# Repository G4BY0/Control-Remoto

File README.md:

# Remote Controller

### A literal super universal remote controller, you can manipulate TVS, AIR CONDITIONERS, DECODERS and MORE.

The purpose of this project is to have in one room, one infrared remote for everything.

https://github.com/G4BY0/Control-Remoto/blob/af7007d788a45e271489a508236b302a6bf80a4f/Picture.jpeg

## Contents

  -[How it works?](#how-it-works?)
  -[Development Status](#development-status)
  -[Hardware](#hardware)
  -[Dependencies](#dependencies)

## How it works? (Software)

The structure of the stored Infrared signals is:

Example:

* Profile: LG TV
* Subprofile: Turn on

This kind of profiles are stored on the SD, they are separated in diferent files.

Example: LG_TV.db

This files have the binary of infrared signals with the name of their subprofiles.

## Development Status

Latest Stable Release    

Latest Development Release    

## Hardware

* [PCB](https://github.com/G4BY0/Control-Remoto/tree/main/hardware)
* Display Adafruit SH110X
* Six Botons
* [Nodemcu Esp32-S (4MB Flash Memory)](https://docs.ai-thinker.com/_media/esp32/docs/nodemcu-32s_product_specification.pdf)
* Module SD (3.3V, We modded it to work with that voltage)
* BC548 (Battery Medition)
* VS1838 (Infrared Receiver)
* Infrared LED (Infrared Emitter)
* LIPO Battery 3.7-4.2V
* Step Up 1.8v-4.2v to 5V (180mA)
* LIPO Charger USB-C Port
* 2N3904
* Resistors 10K, 10K, 630K (Battery Medition)
* [Six Keycaps](https://github.com/G4BY0/Control-Remoto/tree/main/hardware/STL's)
* [Case](https://github.com/G4BY0/Control-Remoto/tree/main/hardware/STL's)
* Cable USB-C for charging

## Dependencies

* [Adafruit BusIO](https://github.com/adafruit/Adafruit_BusIO)
* [Adafruit GFX Library](https://github.com/adafruit/Adafruit-GFX-Library)
* [Adafruit SH110X](https://github.com/adafruit/Adafruit_SH110x)
* [QRCode](https://www.adafruit.com/products/2471)
* [arduino-esp32](https://www.adafruit.com/products/2471)

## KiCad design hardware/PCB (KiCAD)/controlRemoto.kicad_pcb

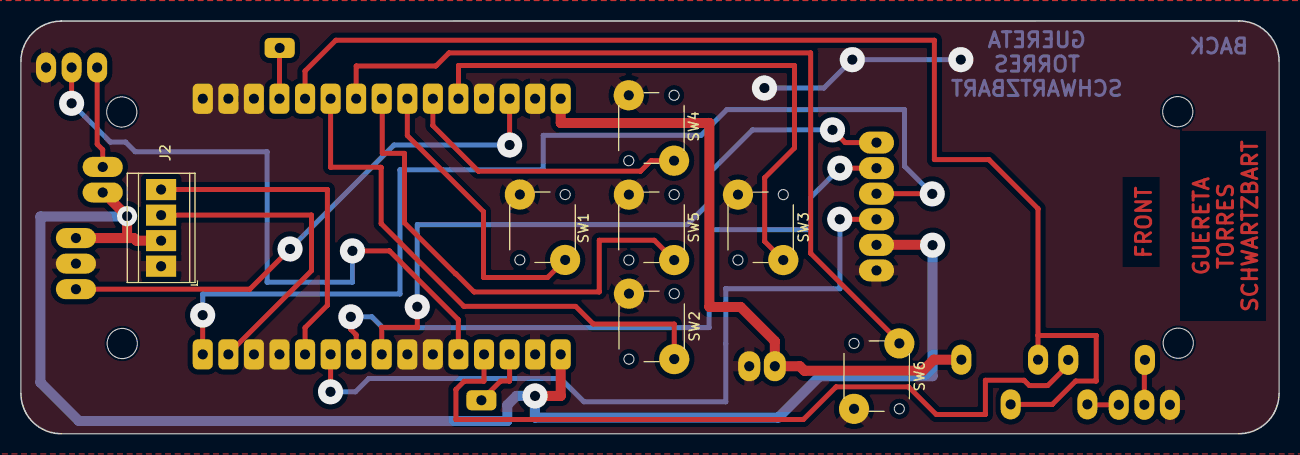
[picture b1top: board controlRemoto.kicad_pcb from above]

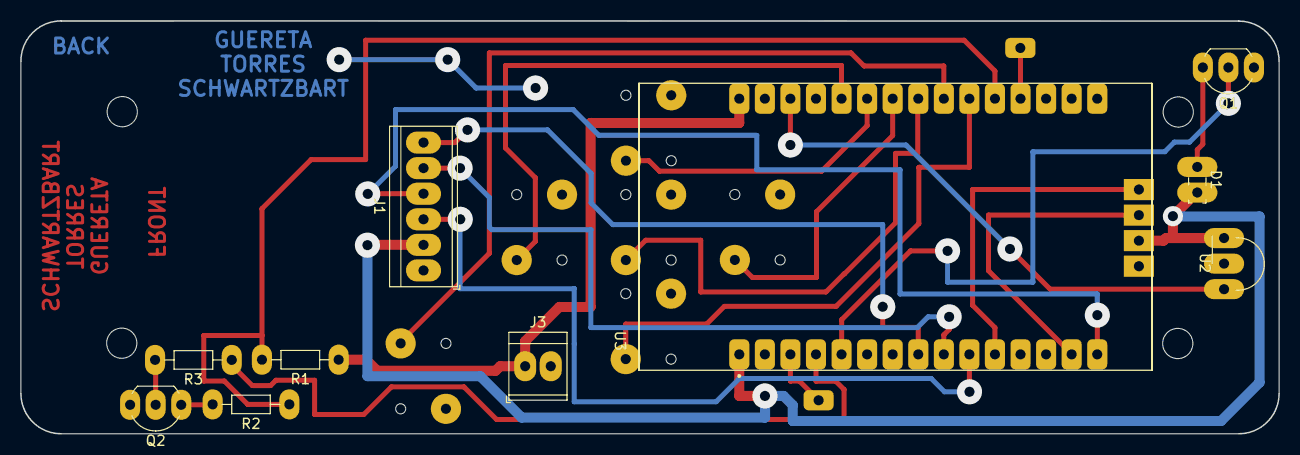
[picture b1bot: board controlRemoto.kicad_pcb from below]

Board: 2 copper layers, 125.0 x 41.0 mm, 17 parts (10 on the bottom side), 22 nets.

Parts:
D1: IR EMISOR; LED_SideEmitter_Rectangular_W4.5mm_H1.6mm
J1: Modulo SD; TerminalBlock_TE_282834-6_1x06_P2.54mm_Horizontal
J2: Display Oled; TerminalBlock_TE_282834-4_1x04_P2.54mm_Horizontal
J3: Bornera; TerminalBlock_TE_282834-2_1x02_P2.54mm_Horizontal
Q1: 2N3904; TO-92_Inline_Wide
Q2: BC546; TO-92_Inline_Wide
R1, R2: 10000; R_Axial_DIN0204_L3.6mm_D1.6mm_P7.62mm_Horizontal
R3: 630000; R_Axial_DIN0204_L3.6mm_D1.6mm_P7.62mm_Horizontal
SW1: ARRIBA; SW_PUSH_6mm_H4.3mm
SW2: IZQUIERDA; SW_PUSH_6mm_H4.3mm
SW3: ABAJO; SW_PUSH_6mm_H4.3mm
SW4: DERECHA; SW_PUSH_6mm_H4.3mm
SW5: ENTER; SW_PUSH_6mm_H4.3mm
SW6: ATRAS; SW_PUSH_6mm_H4.3mm
U2: IR RECEIVER; Vishay_MINIMOLD-3Pin
U3: ESP32-DEVKIT-V1; MODULE_ESP32_DEVKIT_V1

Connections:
3V3: D1.2 (A), J1.2, J2.2, U2.3 (Vs), U3.1 (3V3)
+3V8: J3.1, R1.1, U3.30 (VIN)
D2: R3.1, U3.4 (D2)
D4: Q1.2 (B), U3.5 (D4)
D5: J1.6, U3.8 (D5)
D13: U2.1 (OUT), U3.28 (D13)
D14: SW3.1, U3.26 (D14)
D18: J1.5, U3.9 (D18)
D19: J1.3, U3.10 (D19)
D21: J2.4, U3.11 (D21)
D22: J2.3, U3.14 (D22)
D23: J1.4, U3.15 (D23)
D25: SW5.1, U3.23 (D25)
D26: SW1.1, U3.24 (D26)
D27: SW4.1, U3.25 (D27)
D32: SW2.1, U3.21 (D32)
D33: SW6.1, U3.22 (D33)
D35: R1.2, R2.1, U3.20 (D35)
GND: J1.1, J2.1, J3.2, Q1.1 (E), Q2.3 (E), SW1.2, SW2.2, SW3.2, SW4.2, SW5.2, SW6.2, U2.2 (GND), U3.2 (GND), U3.29 (GND)
unnamed: D1.1 (K), Q1.3 (C)
unnamed: Q2.2 (B), R3.2
unnamed: Q2.1 (C), R2.2

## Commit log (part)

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2023-03-07 Inicio de Proyecto
    Estableciendo parámetros iniciales, ordenando y usando herramientas planteadas en la materia Proyecto Final
2023-03-07 Desarrollado en clase
    Plasme lo desarrollado en clase para luego continuarlo en el instituto
2023-03-07 Desarrollando clase
    Incluyendo librerias y ordenando un toque.
2023-03-07 desarrollo en clase + tutorial
    Introduccion de clases de gaby a melvin y joaco, melvin propuso buenas ideas de la interfaz del tft "los menus"
2023-03-10 Ordenando
2023-03-16 Cambiazo de Display
    Cambiamos de Display TFT 2.2" a OLED 1.3"
2023-03-26 Change of library for driver of display
    display 1.3" OLED
2023-03-26 Desarrollando
2023-03-28 Desarrollando Cursor
2023-03-31 Developing
2023-04-01 Developing
    desarrollo del cursor
2023-04-04 Developing
    Desarrollo en clase 04/04/23
2023-04-06 Developing
    Desarrollo
2023-04-06 Developing
    Desarrollando con los pibes
2023-04-09 Developing
    Desarrollando
2023-04-09 Optimizando
2023-04-10 Developing
    Desarrollando y separando de manera intuitiva el codigo para facil comprension
2023-04-10 Updateado lo que joaco me corrigio
2023-04-10 Ordenando y desarollando
    Infrarrojo, planeando como va a laburar
2023-04-13 Developing
    soy guereta pero desde la cuenta de melvin :))
2023-04-17 Developing
    Desarrollando en grupo
2023-04-20 Developing
    Subo cambios por si hay algun boludo que tiene ganas de molestar, dejaron el celu en porteria porque me lo olvide en el auto y me voy un toq, ahora sigo desarrollando en un rato.
2023-04-21 Ordenando y Arreglando
    arreglando errores y ordenando parte del codigo
2023-04-21 Developin
    desarrollanod
2023-04-24 Ordenando
    Ordenando
2023-04-25 Developping & Fixxing
    Desarrollando y corrigiendo errores
2023-04-27 License
    MIT LICENSE
2023-05-04 Developing
    Desarrollando el manejo de perfiles
2023-05-05 Discutiendo
    Discutiendo como va a ser el desarrollo de los subperfiles y que en la version beta del proyecto, el nombre de los subperfiles va a estar limitado hasta 12 caracteres.
2023-05-11 Developing
    Desarrollando crear y eliminar subperfiles, falta desarrollar un poco mas y tambien el apartado del almacenamiento de los subperfiles para agregar y eliminar
2023-05-14 Cursor WritterV2 + Developing
    Desarrollo de otra clase de Writter y desarrollo en el codigo
2023-05-14 Cursor
    Me olvide de incluir los cambios de Cursor.h
2023-05-16 Developing
    Desarrollando en equipo
2023-05-16 Cambio de pines en el infrarrojo
    Un cambio pequeño pero a la vez crucial
2023-05-16 Pre-Alpha (Modos)
    Configuracion de modos hecha para la version Pre-Alpha
2023-05-21 Developing & Searching for Errors
    Sigo buscando el error de indefiniciones cuando se compila, agregue un par de features mas
2023-05-21 Desarrollando y fixeando bugs
    Problema al terminar el compilado:
    Advanced Memory Usage is available via "PlatformIO Home > Project Inspect"
    Error: The program size (44552 bytes) is greater than maximum allowed (32256 bytes)
    RAM: [====*** [checkprogsize] Explicit exit, status 1
    ======] 151.8% (used 3109 bytes from 2048 bytes)
    Flash: [==========] 138.1% (used 44552 bytes from 32256 bytes)
2023-05-22 Optimizing
    - Se genero una banda de optimización gracias a que las cadenas de caracteres se pueden almacenar en la memoria flash en vez de la ram (utilizando por ejemplo: F() que devuelve: const __FlashStringHe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
    "F() se utiliza para almacenar cadenas de texto en la memoria de programa (flash) en lugar de la memoria RAM. El tipo devuelto por F() es const __FlashStringHelper*, que es un tipo especial definido 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
    La principal diferencia radica en la ubicación de almacenamiento de la cadena de texto. Mientras que const char* almacena la cadena en la memoria RAM, F() almacena la cadena en la m
2023-05-22 Revert "Revert "Merge branch 'main' of https://github.com/G4BY0/Control-Remoto""
    This reverts commit 4b9f240cd9d582058136f83fae59486e599da04a.
2023-05-22 Optimizando
    Optimizando las mierdas que Guereta deja. Miranda nos sirvió de gran ayuda
2023-05-26 Seteando Configs
    - La librería SD como es incompatible con otras arquitecturas que no son AVR, la desinstale y en caso de usar la placa que tenga AVR se usará esa, sino la otra.
2023-05-31 Developing & Correcting Issues
    Arreglado el problema de reinicio en el setup, pero luego hay otro problema que un nucleo hace dump y resetea el sketch... Solucionar pronto
    Guru Meditation Error: Core 1 panic'ed (LoadProhibited). Exception was unhandled.
    Core 1 register dump:
    PC : 0x40087818 PS : 0x00060e30 A0 : 0x800d8014 A1 : 0x3ffb2190
    A2 : 0x00000002 A3 : 0x00000000 A4 : 0x000000ff A5 : 0x0000ff00
    A6 : 0x00ff0000 A7 : 0xff000000 A8 : 0x80104904 A9 : 0x3ffb2150
2023-06-01 IRremote Issues
    Debido a que vamos a usar la placa ESP32S de la marca nodemcu, IRremote no dispone de compatibilidad al esp32... entonces se debera usar otra lamentablemente.
    Esto da lugar a que hay que desarrollar en el apartado de Profiles y Infrared.
2023-06-05 Correcting Issues
    Corrigiendo errores del Writter y WritterV2
2023-06-05 Dev
    Developing & Correcting Issues
2023-06-06 Correcting Issues
    corrigiendo errores en el colegio, sin melvin lamentablemente. porque falto y no aviso >>:(((((
2023-06-13 Desarrollando
    Corrigiendo errores del writter y cursor
2023-06-14 Ordenando y Corrigiendo Errores
    Corrigiendo errores, ordenando y viendo que onda lo del cursor
2023-06-16 Developin Alone :(
    Hoy falto mi equipo, estoy solo en el banco, pero mientras desarrollaba los sentia q me estaban viendo y apoyando asi que los agrego como colaboradores :)
    No pude probar lo del cursor en el programa porque el hardware lo tiene Melvin porque yo soy un salame q se lo olvido ayer en gimnasia... pero estuve corrigiendo algunos sectores de codigo que podian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
2023-06-21 Desarrollo CursorUltimate
    Desarrollando y todavía intentando rescatar el CursorV2 (descubri una forma de hacerlo pero lo tengo que checkear y son las 22:53)
2023-06-22 Developing & Correcting Issues
    En la mañana de hoy se agrego la herramienta std::vector para el movimiento dinamico (en la memoria heap) de los nombres de los perfiles y subperfiles, hay q retocar un par de cosas del Writter y del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
2023-06-23 Comments
    Comentando algunas cosas que no pude comentar en su momento debido a la perdida de cordura que me causaba el tema de que no funcionaba el modulo SD. ufffffff.... 😌😌😌😌😌
2023-06-24 Correcting Issues
2023-06-26 Correcting Issues & Optimizing
2023-06-26 Developing
    Desarrollando pero lo pedido en el pasado commit no. Queda pendiente
2023-06-27 Putting Comments
    Poniendo comentarios por si luego gandulfo hace preguntas, podría poner mas comentarios
2023-06-29 Comments
    Comentando para que se entienda lo mas perfecto posible
2023-06-29 ALL COMMENTED
    Comentado todo el codigo
2023-06-29 Una cosita mas
    Me olvide de cambiarle el nombre a un archivo
2023-06-30 Checking Issues
    Checkeando errores
2023-07-01 Desarrollando
    Mañana sigo viendo q es lo que cause el problema a la hora de almacenar el infrarrojo solo la información, el resto joya. luego de resolver lo del almacenamiento hay que ver de si funciona cuando lo 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
2023-07-02 Correcting Issues
    Errores arreglados:
    - QR Performante (cree una función que recibe un string, y en base como funciona el QR, entrando en menos detalle cuando se decodifica el QR se recibe el string y ese string lo que hace el celu gener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
    - Arregle los bugs del WritterV2 de snd que cuando estaba en mayúscula o símbolos no dejaba marcar como terminado el string.
    - No encontré el por que no abre el archivo del Perfil para almacenar el Subperfil recibido. Después de eso vendría checkear si funca retirarlo del alma
2023-07-03 Feature Sleep
    - Ahi esta el feature de sleep mode, estaría bueno ponerle una imagen de una luna corte de sleeping o algo asi. vi un video piola que lo hace: https://www.youtube.com/watch?v=0KGMFhFQ0YY
    https://animator.wokwi.com/
    Pero prioridad N°1 ahora es encontrar el bug que no me deja almacenar el subperfil.
2023-07-03 dev
    me teng oq ir de excursionm subo esto rapido pero noe esta terminado
2023-07-10 Dev
    - Agregado los Tasks de batería y Sleep (multithreading)
    - Agregue en el Cursor que si se presiona derecha es como si tocara ENTER y si tocara el botón izquierda es como si tocara BACK (es mas intuitivo y no cambia nada ponerlo)
    - (IDEA) Agregar un reloj en el menú principal porque el nodemcu esp32 tiene un RTC incorporado
    - (IDEA) Lo de placas AVR queda descartado por el momento, luego si pinta lo hacemos compatible para este tipo de placas.
    - (BUG) todavía no fue corregido lo del cursor de ir de abajo del todo al primero del todo
    - (BUG) Lo de retirar del almacenamiento el perfil todavia no arreglado
2023-07-10 Issues
    -Algunos errores por compatibilidades.
    - Linea 168 main.cpp Comentario explicado:
    //vTaskStartScheduler(); // Genera un core dump si se permite el uso del void loop() Asegurarse de usar si es que no se usa el void loop()
    - Mañana tengo que reeplantear una forma de como extraer los subperfiles porque no esta bien plataneada la logica y por eso no lee los subperfiles del almacenamiento
2023-07-11 Arreglado lo del Watch Dog Timer
    Nuevo task que refresca el Timer del Watch Dog
2023-07-11 Dev
    Lo subo porque estamos yo y Joaco usando dos maquinas distintas los dos haciendo debugging
2023-07-11 Vuelvo a subir
    Subo Otra vez Para compilar en otra maquina asi es mas rapido
2023-07-11 Dev
    Corrigiendo cosas
    - Problema del perfil invisible
    - Llego a mi casa y testeo con mi aire de mucho mas cerca porque no tenemos el transistor para el emisor
    - Descargue la libreria de RTC para usar el que tiene adentro la placa
2023-07-12 DEV
    Developing
    -No llego a explicar porque ya nos tenemos que ir
2023-07-13 Dev Clock
    Developeando el clock sin Melvin porque esta en practicas.
2023-07-14 DEV
    viendo el consumo de cada task y cviendo lo de la hora y lo del cursor que muestre en que pagina me encuentro
2023-07-16 Ordering
    Ordenando
2023-07-17 Ordering
    Ordenando y luego sigo
2023-08-02 Correcting Bugs
    Arregle bugs de cuando tocas boton back que crasheaba
2023-08-07 Correcting Bugs
    Corrigiendo Bugs y ordenando un toq las cosas y comentando
2023-08-10 Viendo la movida de los iconos para la UI
    Viendo que onda
2023-08-14 Cambiazo a la UI
    -El tiempo se mostrara solo si se logra establecer conexion wifi
    -(dev) la bateria junto a su nivel en porcentaje de carga, se mostrar el simbolito
    -(dev) se deberia mostrar el porcentaje de la sd junto al dibujito. si no esta conectada ninguna SD deberia mostrar otro dibujito
2023-08-14 Dev
    Ordenando desarrollando y corrigiendo cosas. nuevo ordenamiento para el hub:
    -Profiles
    -Edit
    -Help
    -ShutDown
    -Diagnostics
2023-08-29 Editando PCB
    Haciendo pequeños cambios al PCB y subiendo los pdf invertidos para su fabricación.
2023-10-08 Update de pinout
    Tuvimos un problema cuando quisimos usar el HSPI del nodemcu esp32s, entonces tuvimos que rediseñar la placa y al final terminamos usando VSPI para evitar usar el pin GPIO12, que es para strapping y 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
2023-10-09 Actualizacion + correccion de bugs
    problemas solucionados:
    -no funciona receiver -> cuando quiero agregar un subperfil a un perfil no lee la se;al
    -cuando creo un perfil y quiero agregar un subperfil al toque se cancela
    -cuando entra en el modo shutdown se ve la bateria aun y cuando toco un boton no vuelve a arrancar el sistema, como si estuviese congelado
    -diagnostics el problema de ese modo es que muestra la cantidad de espacio libre de memoria erronea
2023-10-17 Añadiendo archivos STL's y PCB
    Los respectivos STL del gabinete y keycaps y también el KiCAD del PCB.
2023-10-18 Changes
    Cambios
